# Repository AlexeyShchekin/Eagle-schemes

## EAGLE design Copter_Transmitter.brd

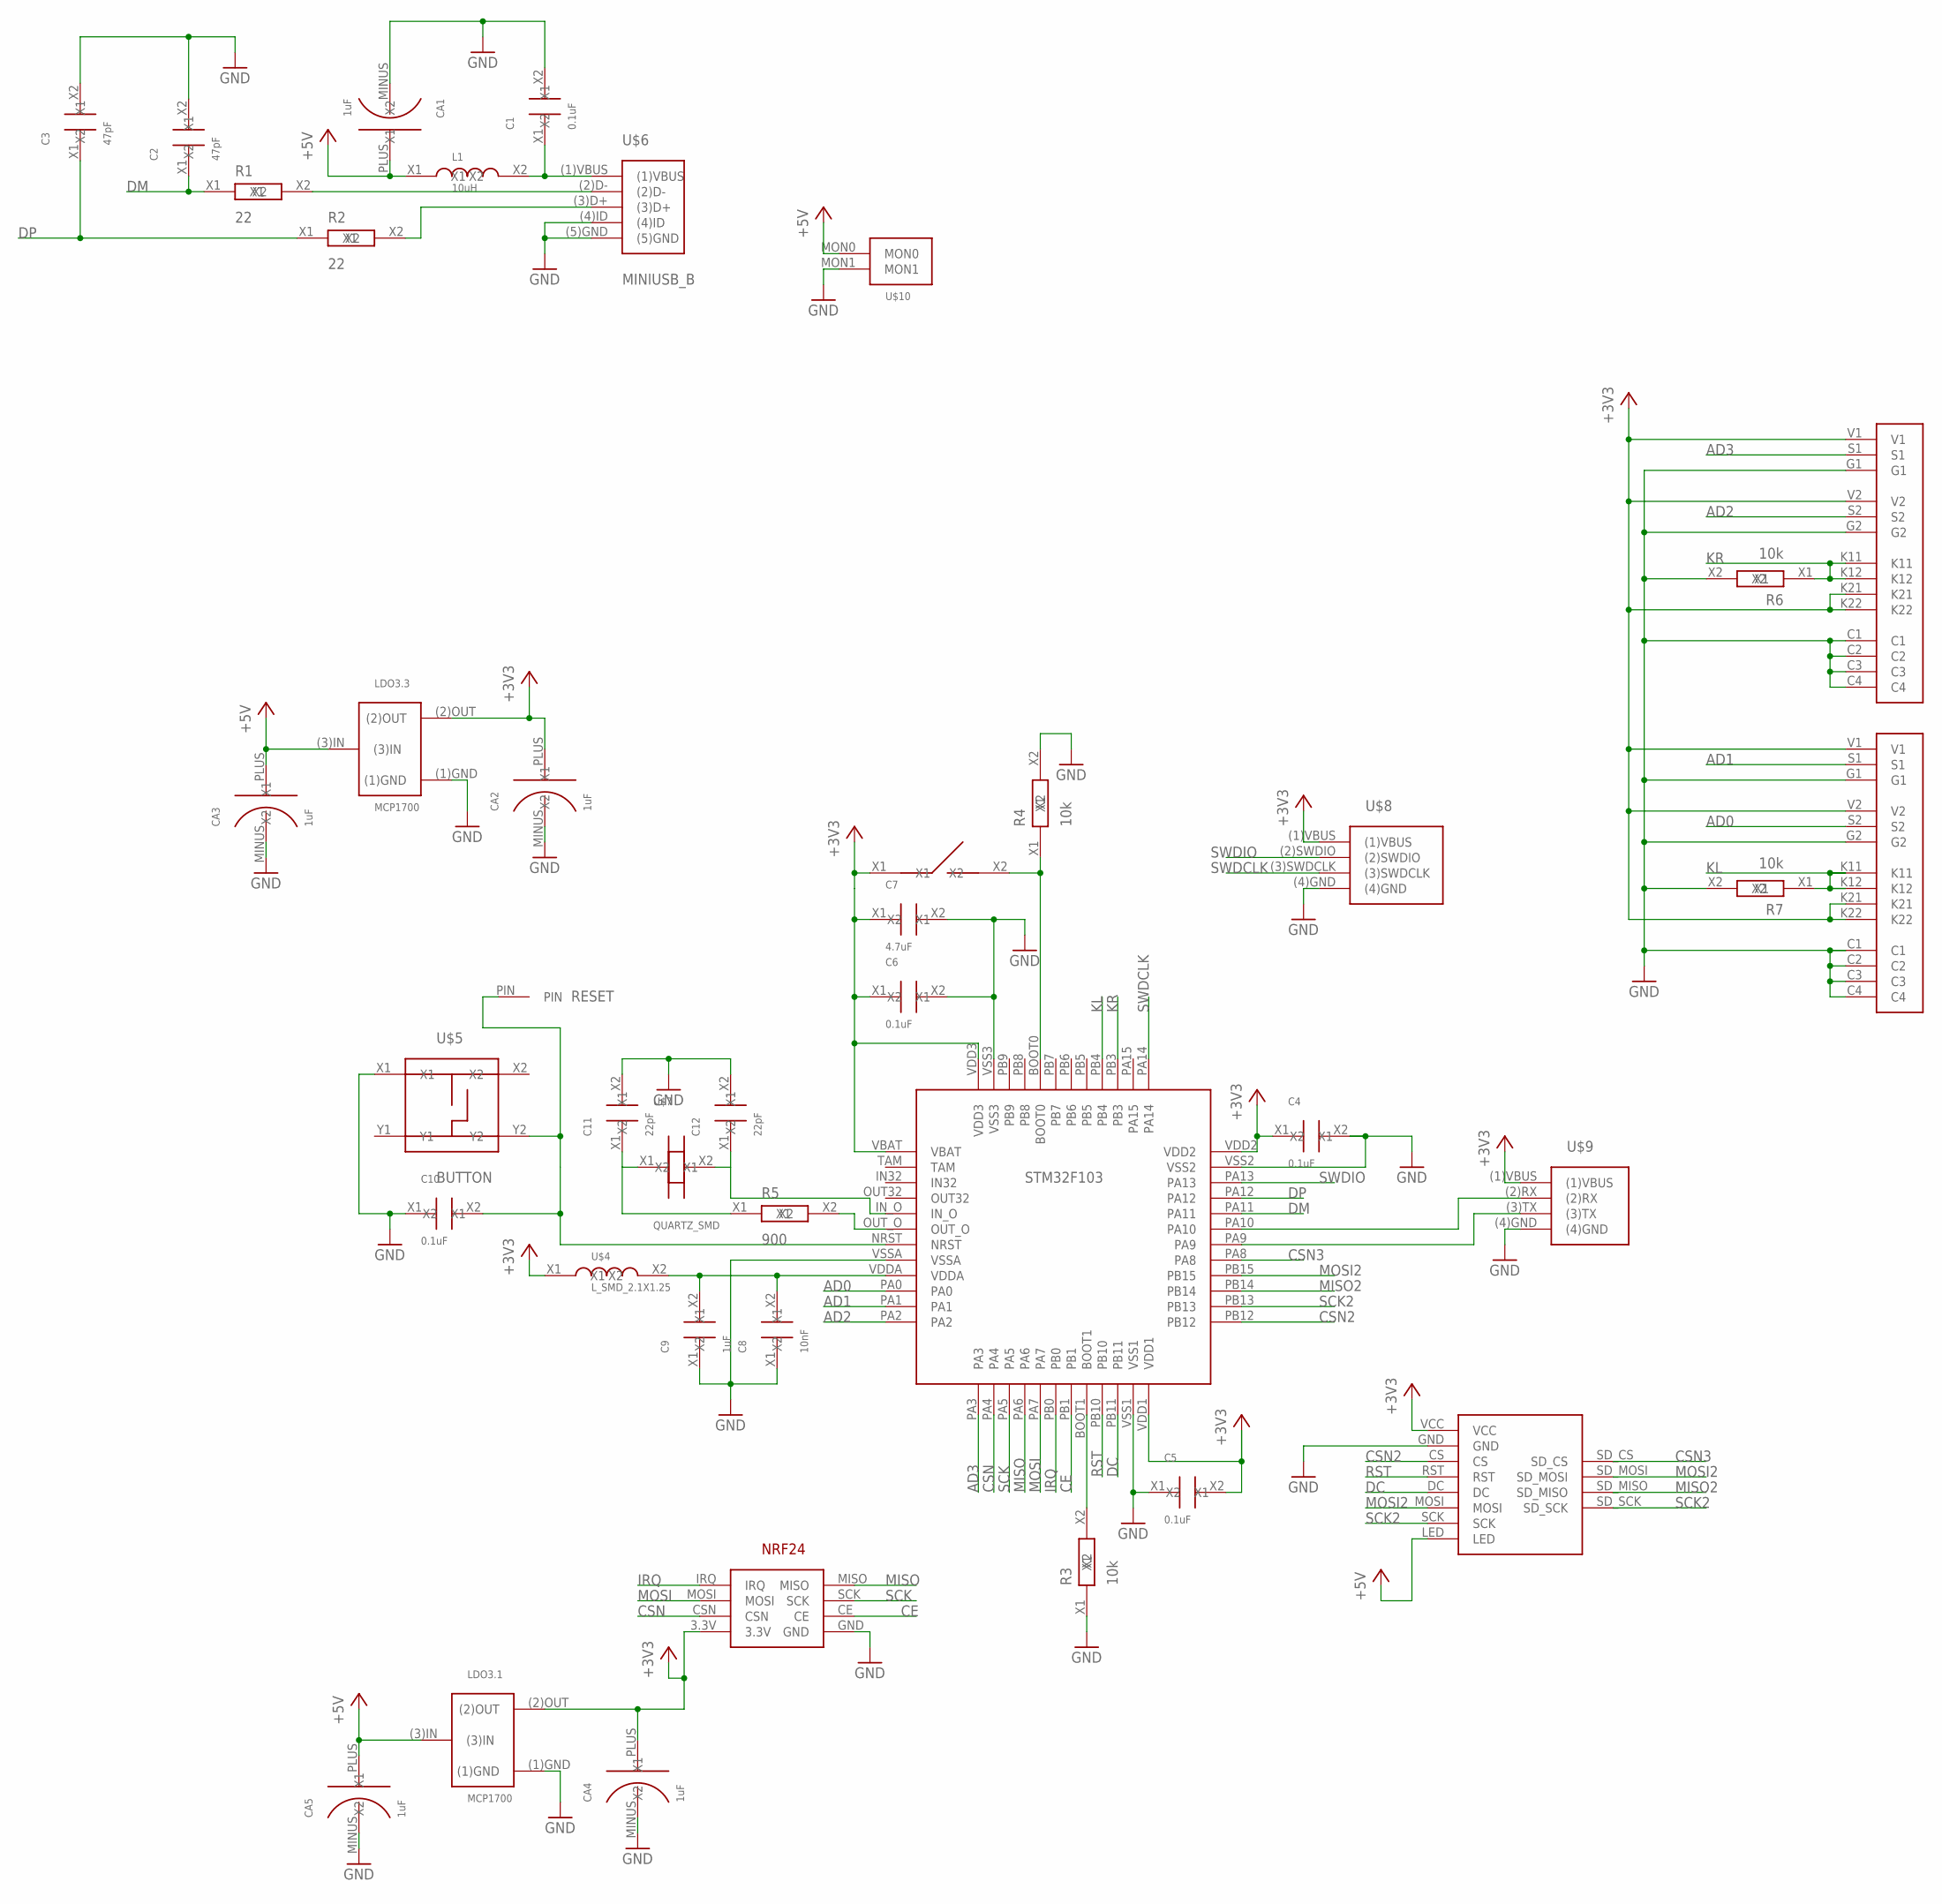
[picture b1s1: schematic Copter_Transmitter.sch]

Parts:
C1, C4, C5, C6, C10: 0.1uF; SMD_2.1X1.25
C2, C3: 47pF; SMD_2.1X1.25
C7: 4.7uF; SMD_2.1X1.25
C8: 10nF; SMD_2.1X1.25
C9: 1uF; SMD_2.1X1.25
C11, C12: 22pF; SMD_2.1X1.25
CA1, CA2, CA3, CA4, CA5: 1uF; C_SMD_TA_A
L1: 10uH; SMD_2.1X1.25
LDO3.1, LDO3.3: MCP1700
R1, R2: 22; SMD_2.1X1.25
R3, R4, R6, R7: 10k; SMD_2.1X1.25
R5: 900; SMD_2.1X1.25
RESET: PIN
STM32F103: STM32F103CBT6
U$1: TFT1.8_SD
U$2: NRF24_PLUG
U$3: DIP_1
U$4: L_SMD_2.1X1.25; SMD_2.1X1.25
U$5: BUTTON
U$6: MINIUSB_B
U$7: QUARTZ_SMD
U$8: SWD
U$9: USART
U$10: MON2PIN
U$11, U$12: JOYSTICK_MINI

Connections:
+3V3: C4.X1, C5.X2, C6.X1, C7.X1, CA2.PLUS (X2), CA4.PLUS (X2), LDO3.1.(2)OUT, LDO3.3.(2)OUT, STM32F103.VBAT, STM32F103.VDD1, STM32F103.VDD2, STM32F103.VDD3, U$1.VCC, U$2.3.3V, U$3.X1, U$4.X1, U$8.(1)VBUS, U$9.(1)VBUS, U$11.K21, U$11.K22, U$11.V1, U$11.V2, U$12.K21, U$12.K22, U$12.V1, U$12.V2
+5V: CA1.PLUS (X2), CA3.PLUS (X2), CA5.PLUS (X2), L1.X1, LDO3.1.(3)IN, LDO3.3.(3)IN, U$1.LED, U$10.MON0
AD0: STM32F103.PA0, U$11.S2
AD1: STM32F103.PA1, U$11.S1
AD2: STM32F103.PA2, U$12.S2
AD3: STM32F103.PA3, U$12.S1
CE: STM32F103.PB1, U$2.CE
CSN: STM32F103.PA4, U$2.CSN
CSN2: STM32F103.PB12, U$1.CS
CSN3: STM32F103.PA8, U$1.SD_CS
DC: STM32F103.PB11, U$1.DC
DM: C2.X1, R1.X1, STM32F103.PA11
DP: C3.X1, R2.X1, STM32F103.PA12
GND: C1.X2, C2.X2, C3.X2, C4.X2, C5.X1, C6.X2, C7.X2, C8.X1, C9.X1, C10.X1, C11.X2, C12.X2, CA1.MINUS (X1), CA2.MINUS (X1), CA3.MINUS (X1), CA4.MINUS (X1), CA5.MINUS (X1), LDO3.1.(1)GND, LDO3.3.(1)GND, R3.X1, R4.X2, R6.X2, R7.X2, STM32F103.VSS1, STM32F103.VSS2, STM32F103.VSS3, STM32F103.VSSA, U$1.GND, U$2.GND, U$5.X1, U$6.(4)ID, U$6.(5)GND, U$8.(4)GND, U$9.(4)GND, U$10.MON1, U$11.C1, U$11.C2, U$11.C3, U$11.C4, U$11.G1, U$11.G2, U$12.C1, U$12.C2, U$12.C3, U$12.C4, U$12.G1, U$12.G2
IRQ: STM32F103.PB0, U$2.IRQ
KL: R7.X1, STM32F103.PB4, U$11.K11, U$11.K12
KR: R6.X1, STM32F103.PB3, U$12.K11, U$12.K12
MISO: STM32F103.PA6, U$2.MISO
MISO2: STM32F103.PB14, U$1.SD_MISO
MOSI: STM32F103.PA7, U$2.MOSI
MOSI2: STM32F103.PB15, U$1.MOSI, U$1.SD_MOSI
unnamed: C1.X1, L1.X2, U$6.(1)VBUS
unnamed: R3.X2, STM32F103.BOOT1
unnamed: R1.X2, U$6.(2)D-
unnamed: R2.X2, U$6.(3)D+
unnamed: R4.X1, STM32F103.BOOT0, U$3.X2
unnamed: R5.X2, STM32F103.OUT_O
unnamed: C11.X1, R5.X1, U$7.X1
unnamed: C12.X1, STM32F103.IN_O, U$7.X2
unnamed: C8.X2, C9.X2, STM32F103.VDDA, U$4.X2
unnamed: STM32F103.PA9, U$9.(3)TX
unnamed: C10.X2, RESET.PIN, STM32F103.NRST, U$5.Y2
unnamed: STM32F103.PA10, U$9.(2)RX
RST: STM32F103.PB10, U$1.RST
SCK: STM32F103.PA5, U$2.SCK
SCK2: STM32F103.PB13, U$1.SCK, U$1.SD_SCK
SWDCLK: STM32F103.PA14, U$8.(3)SWDCLK
SWDIO: STM32F103.PA13, U$8.(2)SWDIO

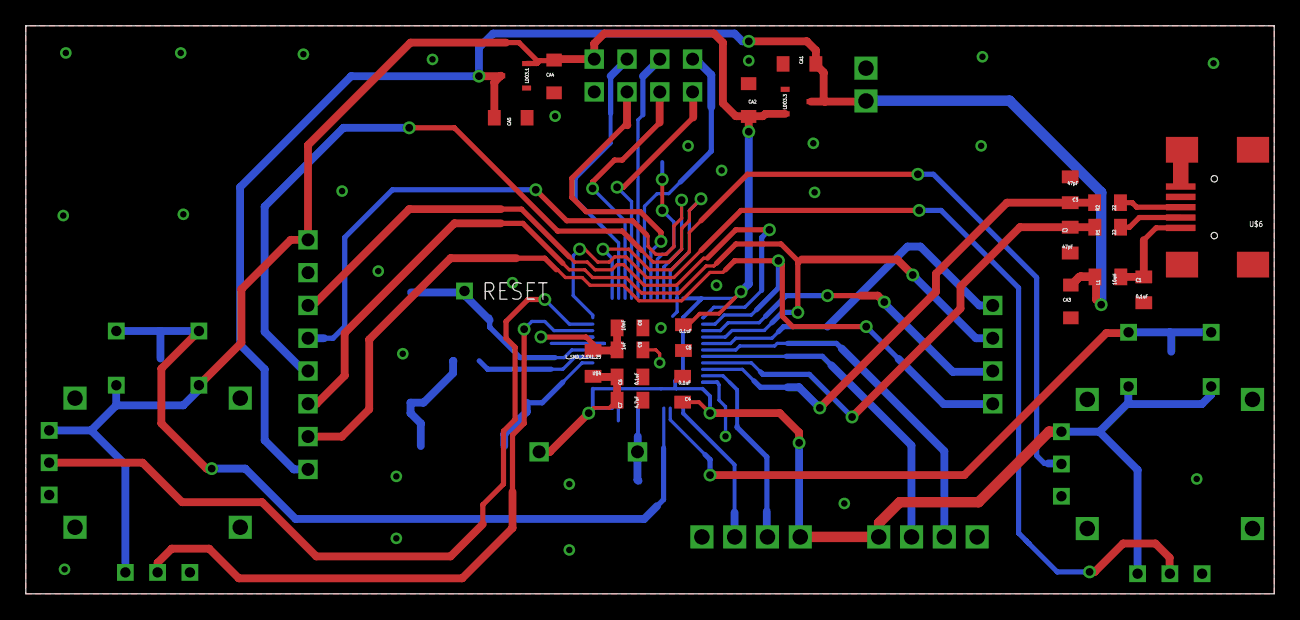
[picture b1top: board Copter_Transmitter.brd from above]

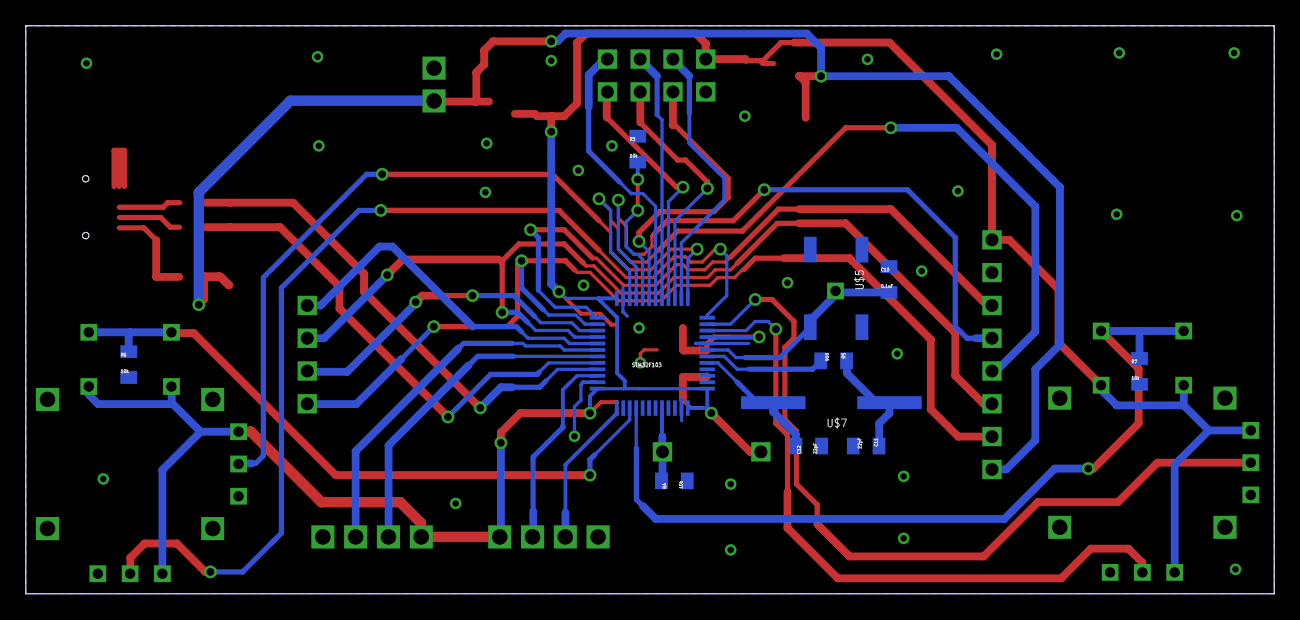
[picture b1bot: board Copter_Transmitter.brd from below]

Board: 2 copper layers, 96.7 x 44.0 mm, 41 parts (11 on the bottom side), 38 nets.

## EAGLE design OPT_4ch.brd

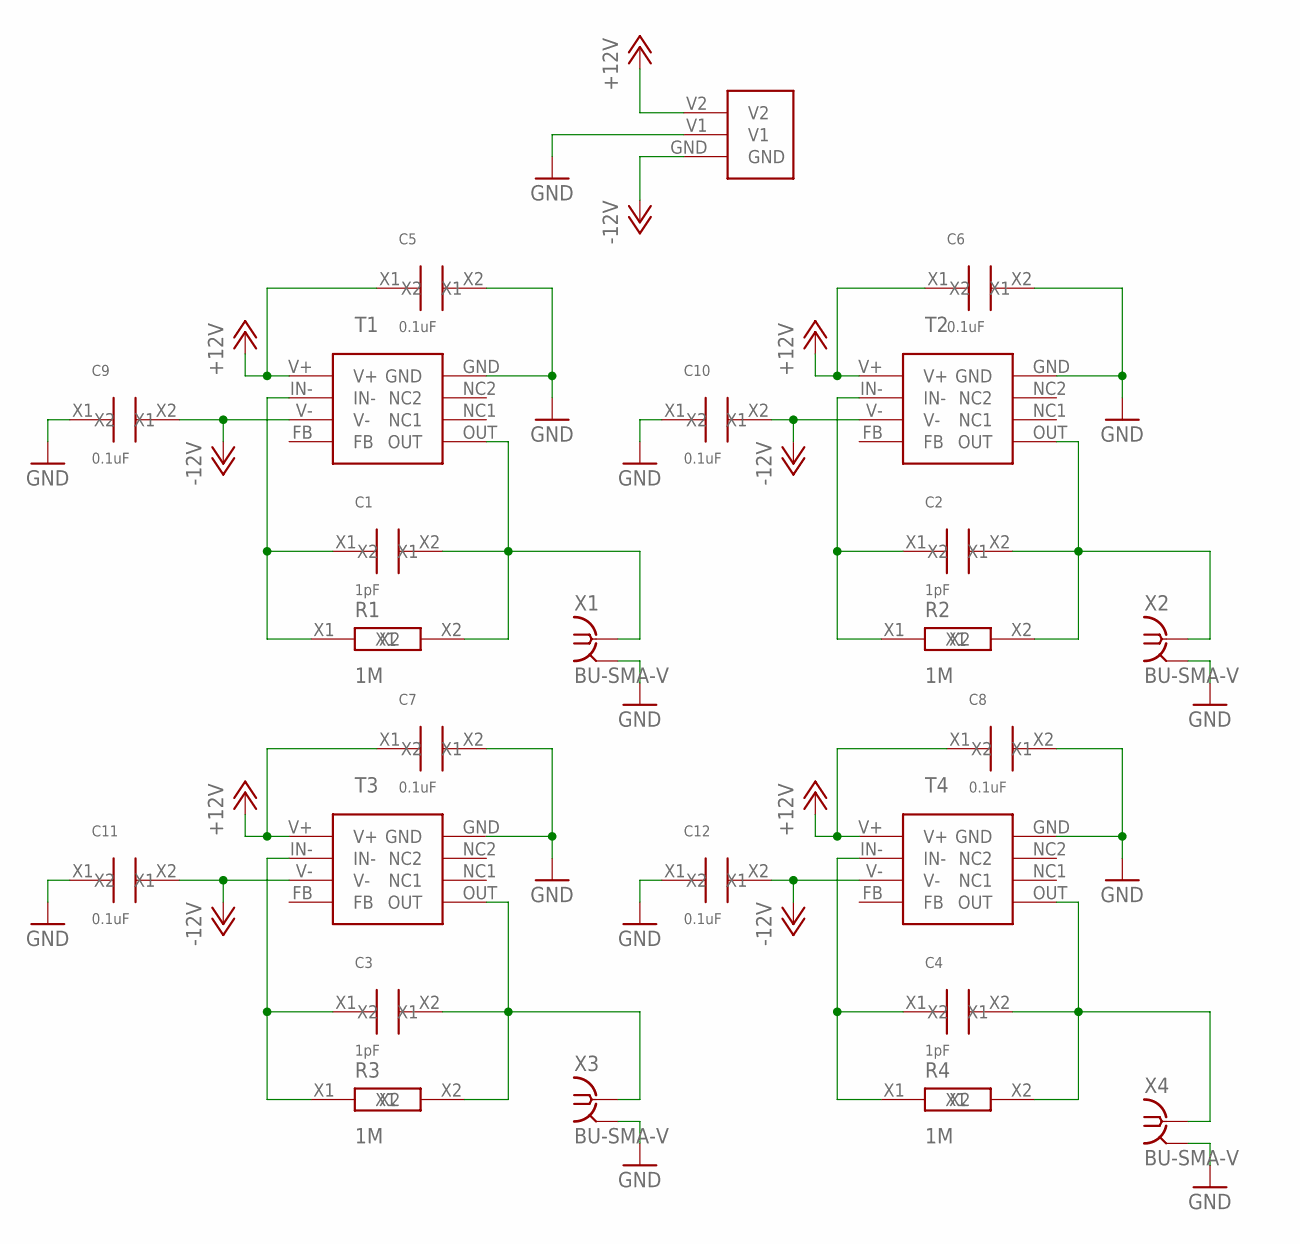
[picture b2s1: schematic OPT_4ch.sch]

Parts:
C1, C2, C3, C4: 1pF; SMD_2.1X1.25
C5, C6, C7, C8, C9, C10, C11, C12: 0.1uF; SMD_2.1X1.25
R1, R2, R3, R4: 1M; SMD_2.1X1.25
T1, T2, T3, T4: OPT101
U$1: BAT3_PLUG
X1, X2, X3, X4: BU-SMA-V

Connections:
+12V: C5.X1, C6.X1, C7.X1, C8.X1, T1.V+, T2.V+, T3.V+, T4.V+, U$1.V2
-12V: C9.X2, C10.X2, C11.X2, C12.X2, T1.V-, T2.V-, T3.V-, T4.V-, U$1.GND
GND: C5.X2, C6.X2, C7.X2, C8.X2, C9.X1, C10.X1, C11.X1, C12.X1, T1.GND, T2.GND, T3.GND, T4.GND, U$1.V1, X1.2, X1.3 (2), X1.4 (2), X1.5 (2), X2.2, X2.3 (2), X2.4 (2), X2.5 (2), X3.2, X3.3 (2), X3.4 (2), X3.5 (2), X4.2, X4.3 (2), X4.4 (2), X4.5 (2)
unnamed: C1.X1, R1.X1, T1.IN-
unnamed: C1.X2, R1.X2, T1.OUT, X1.1
unnamed: C3.X1, R3.X1, T3.IN-
unnamed: C3.X2, R3.X2, T3.OUT, X3.1
unnamed: C2.X1, R2.X1, T2.IN-
unnamed: C2.X2, R2.X2, T2.OUT, X2.1
unnamed: C4.X2, R4.X2, T4.OUT, X4.1
unnamed: C4.X1, R4.X1, T4.IN-

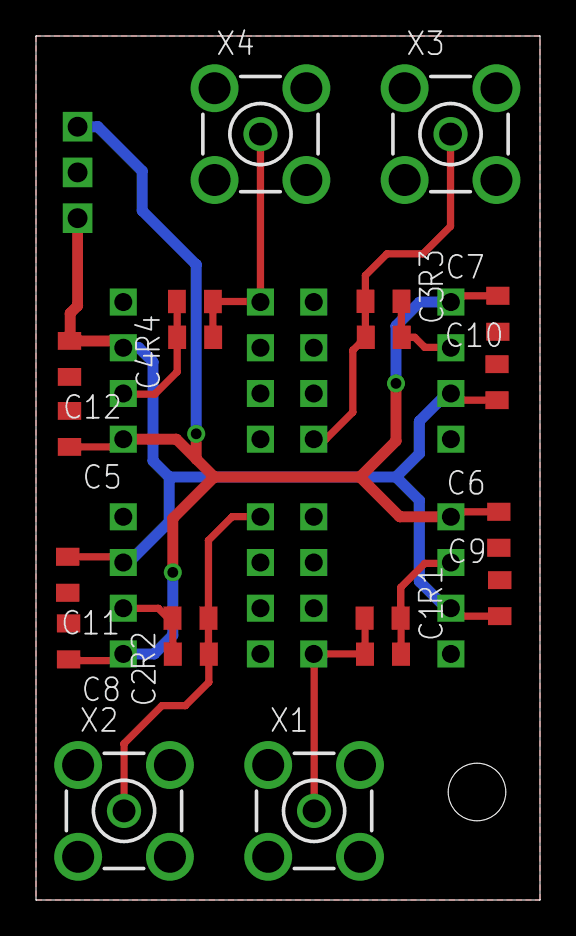
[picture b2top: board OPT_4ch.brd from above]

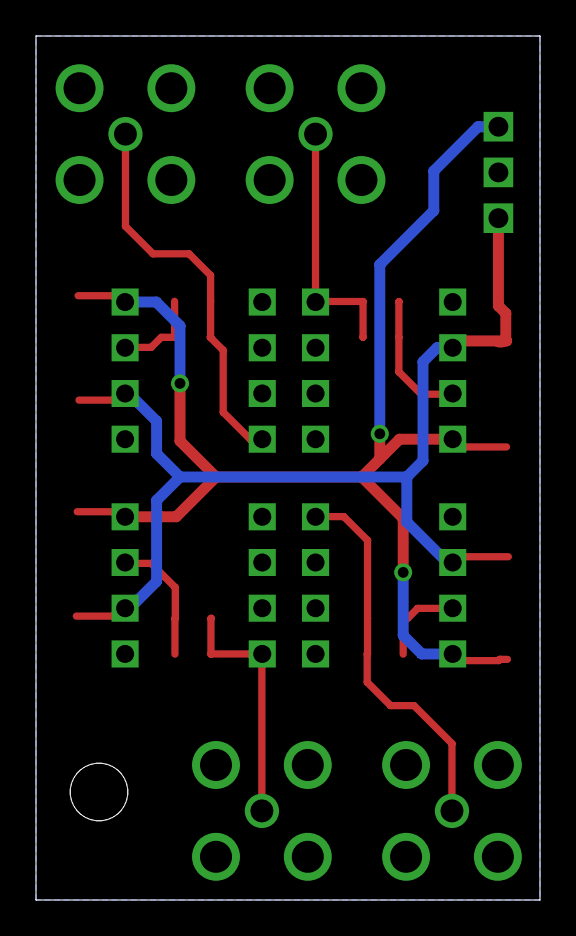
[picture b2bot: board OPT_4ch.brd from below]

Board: 2 copper layers, 28.0 x 48.0 mm, 25 parts (4 on the bottom side), 11 nets.

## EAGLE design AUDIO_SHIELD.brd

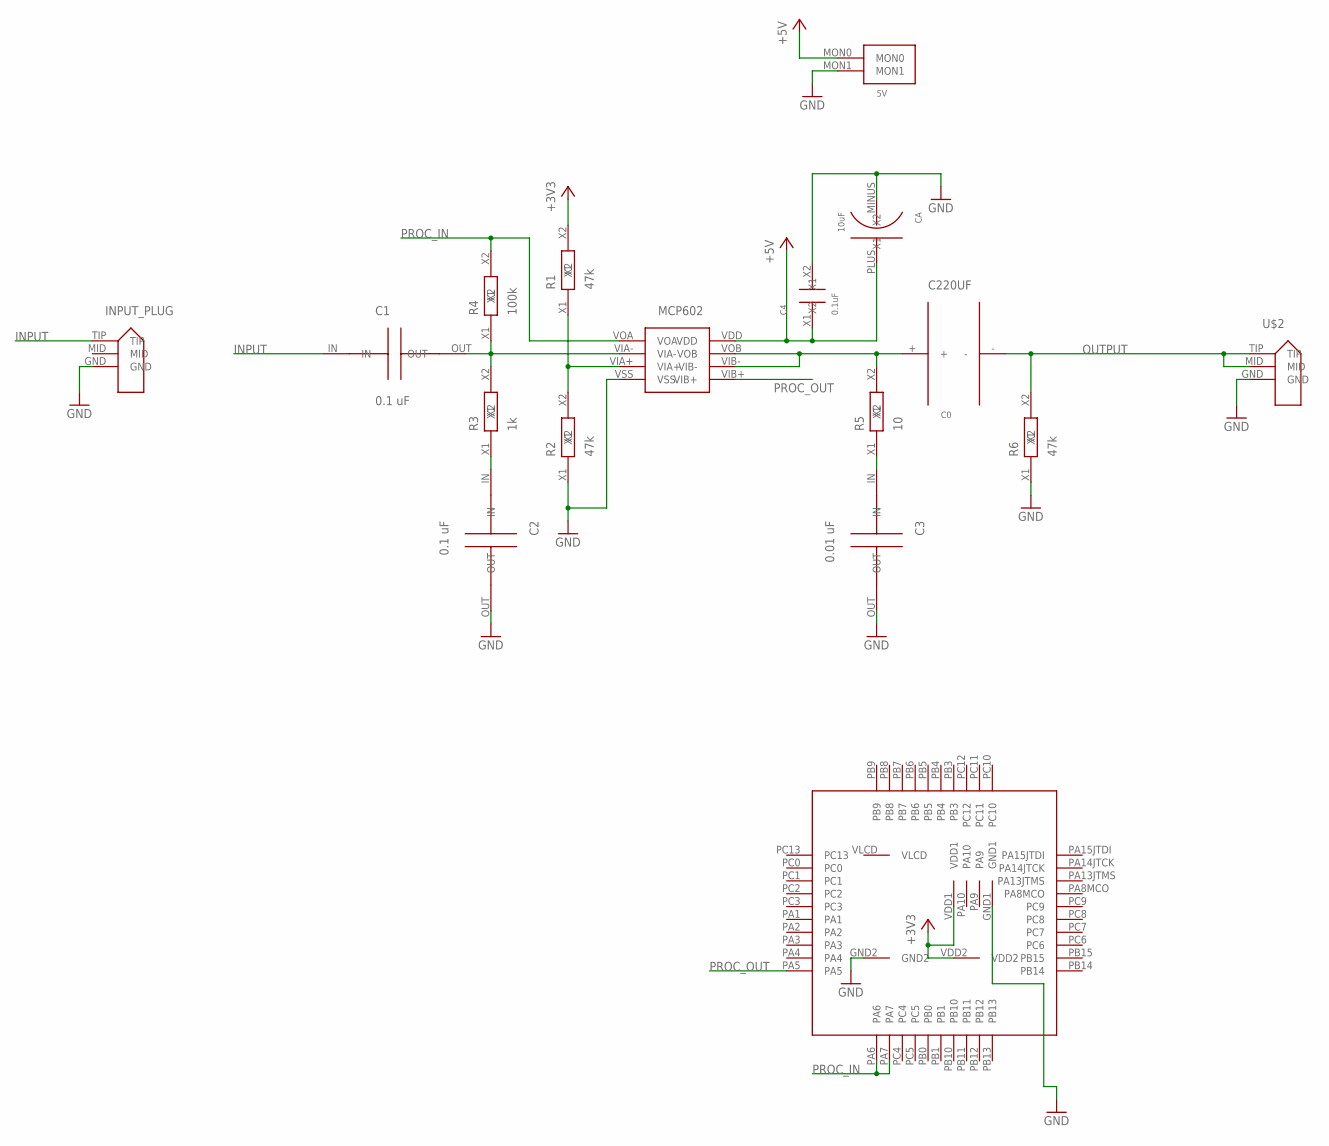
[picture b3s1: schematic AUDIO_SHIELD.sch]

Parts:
5V: MON2PIN
C0: C220UF; C100UF
C1, C2: 0.1 uF; C_CER_5MM
C3: 0.01 uF; C_CER_5MM
C4: 0.1uF; SMD_2.1X1.25
CA: 10uF; C_SMD_TA_A
INPUT_PLUG: AUDIOJACK_ST215N
MCP602: MCP602
R1, R2, R6: 47k; SMD_2.1X1.25
R3: 1k; SMD_2.1X1.25
R4: 100k; SMD_2.1X1.25
R5: 10; SMD_2.1X1.25
U$1: STM32L1_ADAPTER
U$2: AUDIOJACK_ST215N

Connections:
+3V3: R1.X2, U$1.VDD1, U$1.VDD2
+5V: 5V.MON0, C4.X1, CA.PLUS (X2), MCP602.VDD
GND: 5V.MON1, C2.OUT, C3.OUT, C4.X2, CA.MINUS (X1), INPUT_PLUG.GND, MCP602.VSS, R2.X1, R6.X1, U$1.GND1, U$1.GND2, U$2.GND
INPUT: C1.IN, INPUT_PLUG.TIP
unnamed: MCP602.VIA+, R1.X1, R2.X2
unnamed: C2.IN, R3.X1
unnamed: C3.IN, R5.X1
unnamed: C0.+, MCP602.VIB-, MCP602.VOB, R5.X2
unnamed: C1.OUT, MCP602.VIA-, R3.X2, R4.X1
OUTPUT: C0.-, R6.X2, U$2.MID, U$2.TIP
PROC_IN: MCP602.VOA, R4.X2, U$1.PA6, U$1.PA7
PROC_OUT: MCP602.VIB+, U$1.PA5

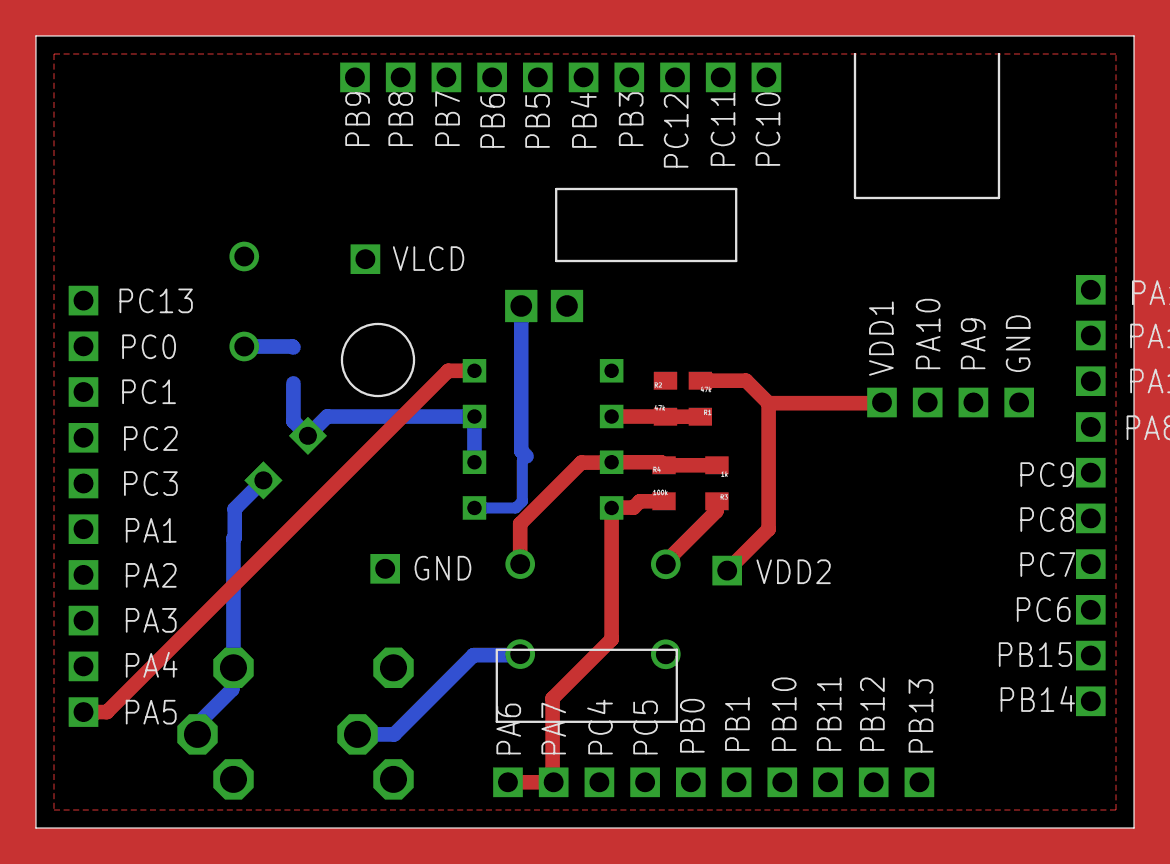
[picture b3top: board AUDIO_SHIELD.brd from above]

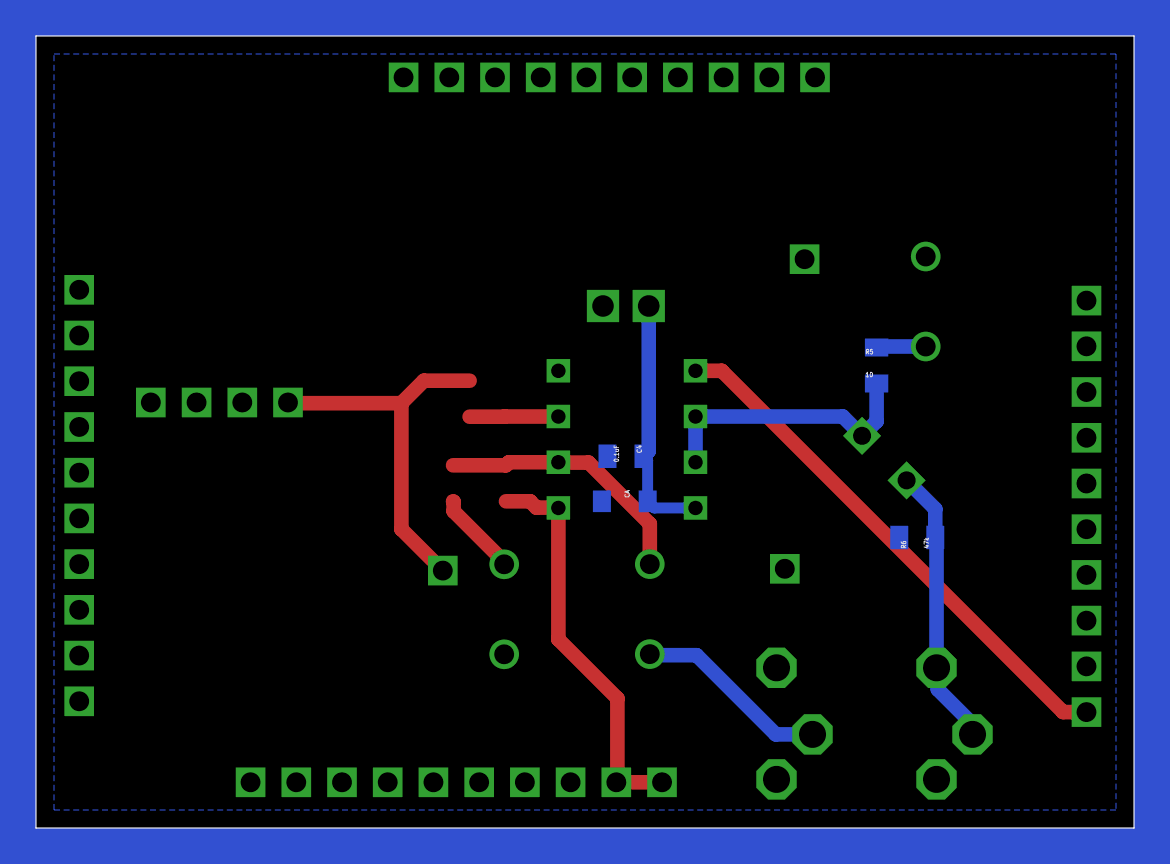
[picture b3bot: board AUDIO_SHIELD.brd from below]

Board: 2 copper layers, 61.0 x 44.0 mm, 17 parts (4 on the bottom side), 12 nets.

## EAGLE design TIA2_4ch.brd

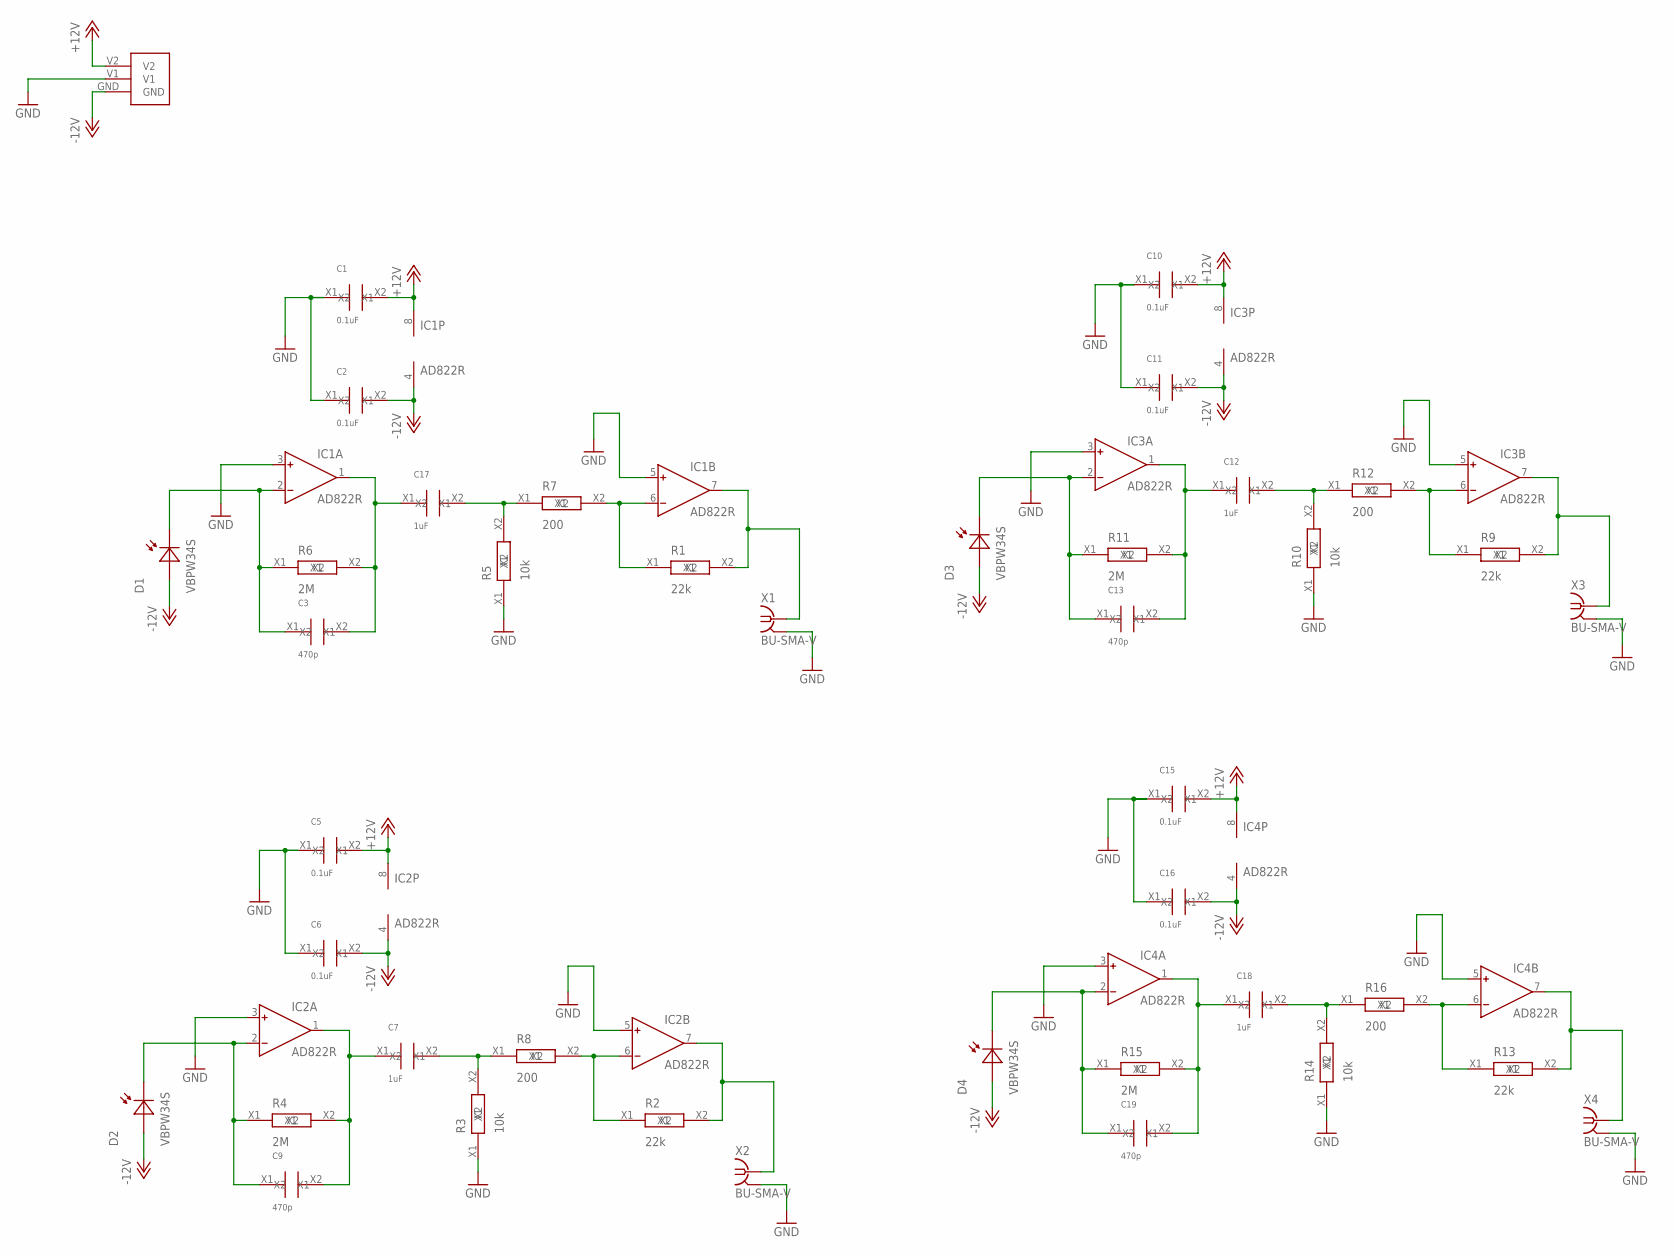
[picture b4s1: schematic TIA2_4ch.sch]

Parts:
C1, C2, C5, C6, C10, C11, C15, C16: 0.1uF; SMD_2.1X1.25
C3, C9, C13, C19: 470p; SMD_2.1X1.25
C7, C12, C17, C18: 1uF; SMD_2.1X1.25
D1, D2, D3, D4: VBPW34S; SOD6439X130N
IC1, IC2, IC3, IC4: AD822R; SO8
R1, R2, R9, R13: 22k; SMD_2.1X1.25
R3, R5, R10, R14: 10k; SMD_2.1X1.25
R4, R6, R11, R15: 2M; SMD_2.1X1.25
R7, R8, R12, R16: 200; SMD_2.1X1.25
U$1: BAT3_PLUG
X1, X2, X3, X4: BU-SMA-V

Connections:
+12V: C1.X2, C5.X2, C10.X2, C15.X2, IC1.8 (V+), IC2.8 (V+), IC3.8 (V+), IC4.8 (V+), U$1.V2
-12V: C2.X2, C6.X2, C11.X2, C16.X2, D1.A, D2.A, D3.A, D4.A, IC1.4 (V-), IC2.4 (V-), IC3.4 (V-), IC4.4 (V-), U$1.GND
GND: C1.X1, C2.X1, C5.X1, C6.X1, C10.X1, C11.X1, C15.X1, C16.X1, IC1.3 (IN+), IC1.5 (IN+), IC2.3 (IN+), IC2.5 (IN+), IC3.3 (IN+), IC3.5 (IN+), IC4.3 (IN+), IC4.5 (IN+), R3.X1, R5.X1, R10.X1, R14.X1, U$1.V1, X1.2, X1.3 (2), X1.4 (2), X1.5 (2), X2.2, X2.3 (2), X2.4 (2), X2.5 (2), X3.2, X3.3 (2), X3.4 (2), X3.5 (2), X4.2, X4.3 (2), X4.4 (2), X4.5 (2)
unnamed: IC2.6 (IN-), R2.X1, R8.X2
unnamed: IC2.7 (OUT), R2.X2, X2.1
unnamed: IC1.6 (IN-), R1.X1, R7.X2
unnamed: IC1.7 (OUT), R1.X2, X1.1
unnamed: C7.X2, R3.X2, R8.X1
unnamed: C9.X1, D2.C, IC2.2 (IN-), R4.X1
unnamed: C7.X1, C9.X2, IC2.1 (OUT), R4.X2
unnamed: IC3.6 (IN-), R9.X1, R12.X2
unnamed: IC3.7 (OUT), R9.X2, X3.1
unnamed: C12.X2, R10.X2, R12.X1
unnamed: C13.X1, D3.C, IC3.2 (IN-), R11.X1
unnamed: C12.X1, C13.X2, IC3.1 (OUT), R11.X2
unnamed: IC4.6 (IN-), R13.X1, R16.X2
unnamed: IC4.7 (OUT), R13.X2, X4.1
unnamed: C18.X2, R14.X2, R16.X1
unnamed: C19.X1, D4.C, IC4.2 (IN-), R15.X1
unnamed: C17.X2, R5.X2, R7.X1
unnamed: C3.X1, D1.C, IC1.2 (IN-), R6.X1
unnamed: C3.X2, C17.X1, IC1.1 (OUT), R6.X2
unnamed: C18.X1, C19.X2, IC4.1 (OUT), R15.X2

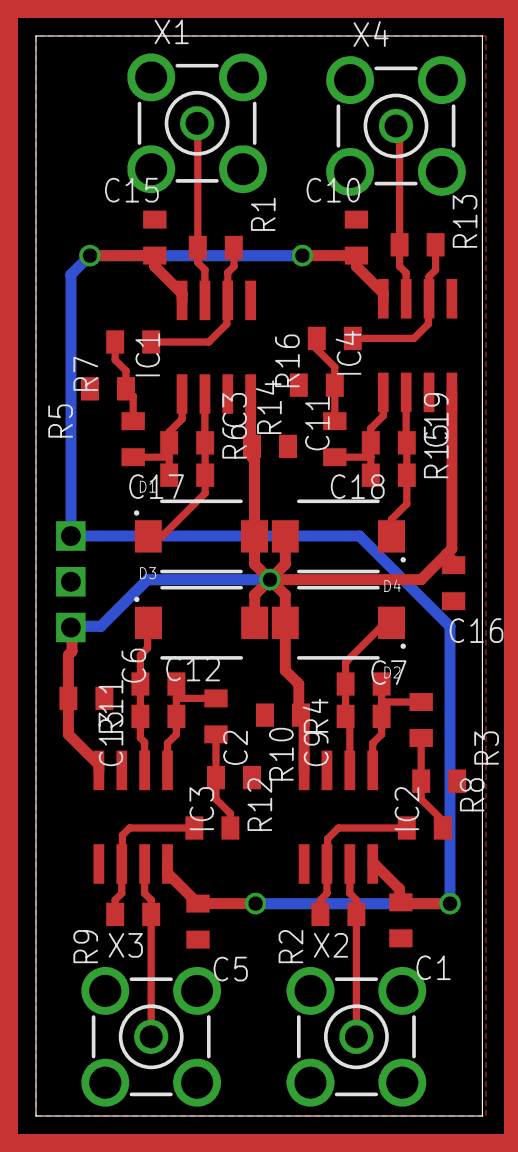
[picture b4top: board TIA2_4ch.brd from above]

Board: 2 copper layers, 24.8 x 60.0 mm, 45 parts (0 on the bottom side), 23 nets.
